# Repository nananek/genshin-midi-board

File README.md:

# RP2040 MIDI → NKRO HID + USB-MIDI

USB MIDI キーボードを USB-A で受け、PC へは NKRO HID キーボード、iPad へは USB-MIDI デバイスとして同時に見せる基板の設計案です。

**RP2040（QFN-56）+ CH345T + 4 層基板**の構成です。外形は **58.0 × 44.0 mm**、四隅 2 mm の 45° パンチカットです。USB-C は長辺に 29.0 mm ピッチで離し、樹脂部が干渉しない余裕を確保します。ケースは無印良品の PP小物ケース M（外寸 64 × 52 × 20 mm、内寸 60 × 46 × 16.5 mm）を使います。加工手順は [docs/case_muji_m.md](docs/case_muji_m.md)、開口用の 1:1 テンプレートは [docs/case_muji_m_template.pdf](docs/case_muji_m_template.pdf) にあります。

> 58.0 × 44.0 mm 基板の配線と検証が完了しました。ERC 0、DRC 0、未接続 0 です。実機検証はまだです。

## 結論

| 項目 | 採用 |
| --- | --- |
| MCU | RP2040 QFN-56 |
| MIDI デバイス側 | CH345T（UART 31250 ↔ USB-MIDI） |
| 基板 | 58.0 × 44.0 × 1.6 mm、4 層、四隅 2 mm パンチカット |
| USB-A | PIO-USB ホスト |
| USB-C 1 | RP2040 native USB、NKRO HID → PC |
| USB-C 2 | CH345T、USB-MIDI → iPad |
| スイッチ | SW1〜SW7（4 × スライド、3 × タクト） |
| 製造 | JLCPCB、4 層、0.5/0.3 mm ビア（最終ホップは 0.45/0.25 mm）、via-in-pad なし |

## 構成の要点

RP2040 の QFN-56 は 0.4 mm ピッチで、外周パッドを外側へ逃がすだけで全ピンを引き出せます。4 層なら GND プレーンを保ちながら標準ビアだけで配線できます。ファームウェアは pico-sdk で、PIO-USB、native USB、UART1 を使います。

詳しい設計は [docs/design.md](docs/design.md) と [docs/decisions.md](docs/decisions.md) を参照してください。データシートとフットプリントの照合は [docs/datasheets.md](docs/datasheets.md) にまとめています。

## 3 ポートの構成

```text
[USB MIDI キーボード]
      │ USB-A (J2)
      ▼
  PIO-USB host (GP12/13)
      │
      ├── Note On/Off ──► RP2040 native USB ── USB-C (J1) ──► PC (NKRO HID)
      │
      └── raw MIDI ── UART1 31250 (GP4/5) ──► CH345T ── USB-C (J3) ──► iPad (USB-MIDI)
```

PC と iPad は物理的に別ポートです。PC 側が未接続でも iPad へ MIDI は流れ、iPad 側が未接続でも PC へ HID は流れます。基板の電源は J1 または J3 の VBUS からダイオード OR で取ります。

## 基板外形とコネクタ

```text
         J1 USB-C (PC)              J3 USB-C (iPad)
         x=15.0                     x=44.0
    ┌────┐                            ┌────┐
    │    │        SW5 RESET           │    │
    │    │           ●                │    │
    ├────┴────────────────────────────┴────┤
    │                                       │
 SW1│                                       │SW3
 SW2│          RP2040 / flash              │
    │          CH345 / power               │
    │                                       │
    ├────┬────────────────────────────┬────┤
    │SW4 │        J2 USB-A            │    │
    └────┘    (MIDI キーボード)        └────┘
```

- 基板: 58.0 × 44.0 mm、t1.6 mm、4 層、四隅 2 mm の 45° パンチカット
- J1/J3: 上長辺、中心間 **29.0 mm**
- J2: 下長辺、USB-A レセプタクル。開口は基板端に合わせる
- J1/J3 の口は基板端から外へ出す。ケースの上壁に 2 か所、下壁に 1 か所の開口を開ける
- Type-C を 10 mm ピッチに寄せるとケーブルの樹脂部が干渉する。今回は同じ失敗を避けるため、29 mm ピッチを確保する

## スイッチ

スイッチは SW1〜SW7 の 7 個です。

| Ref | 部品 | 機能 | 接続 |
| --- | --- | --- | --- |
| SW1 | NKK 115643 スライド | 原神モード（HID ミュート） | GP28 ↔ GND |
| SW2 | NKK 115643 スライド | 楽器モード（スメール音階） | GP15 ↔ GND |
| SW3 | NKK 115643 スライド | サステイン（CC64） | GP27 ↔ GND |
| SW4 | NKK 115643 スライド | USB-A VBUS 手動 ON/OFF | TPS2553 EN 制御 |
| SW5 | DTS-63-N-V-BLK タクト | MIDI リセット（CC123/CC121） | GP14 ↔ GND |
| SW6 | C&K KMR2 SMD タクト | BOOT（QSPI_SS を 1k 経由で GND） | QSPI_SS ↔ GND |
| SW7 | C&K KMR2 SMD タクト | RUN リセット | RUN ↔ GND |

スライドスイッチは 3 ピン品の中央コモンを GPIO、片側を GND、残りを NC にします。GPIO は内部プルアップ、アクティブ LOW、20 ms デバウンスです。SW5 は片側 2 ピンを GND、反対側 2 ピンを GP14 に束ねます。SW6/SW7 は小さな SMD タクトで、ケースの蓋から押します。

## ファイル構成

```text
README.md                         この文書
AGENTS.md                         作業ルール（製造データの配布を含む）
docs/design.md                    詳細設計（電源、ピン、回路、配置）
docs/decisions.md                 設計判断と採用理由
docs/datasheets.md                IC のデータシート、LCSC 型番、CPL 回転の確認
docs/ic_footprints.md             IC フットプリント照合（生成物）
docs/jlcpcb.md                    JLCPCB 向け製造制約と発注チェック
docs/firmware.md                  ファームウェアの実装メモ
docs/case_muji_m.md               無印 PP小物ケース M の加工手順
docs/case_muji_m_template.pdf     開口位置の 1:1 テンプレート
docs/case_muji_m_template.svg     同じテンプレートの SVG
hardware/rp2040_midi_bridge/design.yaml 設計の単一ソース
hardware/rp2040_midi_bridge/pinmap.csv  ピン割り当て
hardware/rp2040_midi_bridge/bom.csv     BOM
hardware/rp2040_midi_bridge/floorplan.svg 配置検討図（生成物）
firmware/include/board_pins.h     ファームウェア用ボード定義
scripts/gen_floorplan.py          配置図生成
scripts/export_ic_footprints.py   IC フットプリント照合の生成
scripts/check_design.py           設計制約チェック
tests/test_design.py              設計制約の単体テスト
```

## 検証

```sh
make check          # 設計制約チェック + 単体テスト
make floorplan      # hardware/rp2040_midi_bridge/floorplan.svg を再生成
make silk           # 基板名、USB-A のピン名、裏面 QR を更新
make case-template  # ケース開口の 1:1 PDF / SVG を再生成
```

`make check` は次を確認します。

- 基板寸法、層数、パンチカット
- USB-C 2 ポートのピッチとエッジ余裕
- ビア径・ドリル径（0.5/0.3 mm と 0.45/0.25 mm、0.15/0.2 mm なし）
- via-in-pad / plugged via の禁止
- ピン割り当ての重複
- スイッチ 7 個の機能と接続
- BOM の SMT 部品に LCSC 型番があること

## 製造データの配布

ガーバー、ドリル、BOM、CPL は設計データとは分けて扱います。リポジトリにはコミットせず、検証済みのリビジョンだけをリリースとして配布します。`make fab VERSION=v0.1.0` で、JLCPCB にそのままアップロードできる Gerber ZIP、BOM、CPL を `dist/` に作ります。Gerber ZIP は展開せず PCB のアップロードへ、BOM と CPL は SMT の欄へ個別に渡します。手順と禁止事項は [AGENTS.md](AGENTS.md) にまとめています。

## ライセンス

[MIT](LICENSE) です。`hardware/rp2040_midi_bridge/lib/` の KiCad シンボルは公式 KiCad ライブラリ由来で、CC-BY-SA 4.0（設計への利用例外あり）です。製造データの配布条件は [AGENTS.md](AGENTS.md) を参照してください。

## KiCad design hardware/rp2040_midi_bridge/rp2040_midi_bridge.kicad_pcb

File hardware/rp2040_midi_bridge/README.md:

# RP2040 MIDI bridge 基板（設計検討）

58.0 × 44.0 mm、4 層、RP2040 + CH345T の設計検討データです。回路図は `rp2040_midi_bridge.kicad_sch` にあり、ERC 0 で通ります。PCB は 58.0 × 44.0 mm の配置で配線済みです。

## 状態

- 外形、配置、回路図、ネットリスト、配線は 58.0 × 44.0 mm で更新済み
- `drc.rpt`（2026-11-25 時点）は 0 DRC violations / 未接続 0
- ガーバー、BOM、CPL は製造前に `make check`、ERC、DRC を通してから生成する

## ファイル

| ファイル | 内容 |
| --- | --- |
| `design.yaml` | 基板、コネクタ、配置、スイッチ、ピン、BOM、製造ルールの正本 |
| `netlist.yaml` | 72 部品、49 ネットのピン接続。回路図と PCB の共通ソース |
| `pinmap.csv` | ピン割り当て（`design.yaml` から生成） |
| `bom.csv` | BOM（`design.yaml` から生成） |
| `placement.csv` | コネクタと主要部品の配置（`design.yaml` から生成） |
| `floorplan.svg` | 配置・干渉検討図（`scripts/gen_floorplan.py` から生成） |
| `rp2040_midi_bridge.kicad_pro` / `.kicad_sch` | KiCad 10 の回路図プロジェクト（`netlist.yaml` から生成） |
| `sym-lib-table` / `fp-lib-table` | プロジェクトローカルと公式のライブラリ参照 |
| `lib/` | 公式に無いシンボルとフットプリント（`lib/README.md` 参照） |
| `erc.rpt` | `kicad-cli sch erc --severity-all` の結果 |
| `rp2040_midi_bridge.kicad_pcb` | KiCad 10 基板（DRC 0 violations、未接続 0） |
| `drc.rpt` | `kicad-cli pcb drc --severity-all` の結果 |

## 再生成

```sh
make tables
make netlist
make floorplan
make check
```

回路図は `netlist.yaml` から生成します。KiCad 10 のコンテナで実行してください。

```sh
./scripts/kicad.sh python3 hardware/rp2040_midi_bridge/scripts/gen_sch.py
make erc
```

## 外形

- 58.0 × 44.0 mm、t1.6 mm
- 四隅 2 mm の 45° パンチカット
- 固定穴なし

## コネクタ

| Ref | 種類 | 位置 | 役割 |
| --- | --- | --- | --- |
| J1 | USB-C | 上辺 x=15.0 | PC / NKRO HID |
| J3 | USB-C | 上辺 x=44.0 | iPad / USB-MIDI |
| J2 | USB-A | 下辺 x=29.0 | MIDI キーボード |

J1/J3 の中心間は 29.0 mm です。Type-C ケーブルの樹脂部が干渉しない余裕を確保しています。ケースは無印 PP小物ケース M（内寸 60 × 46 × 16.5 mm）で、加工手順は [../../docs/case_muji_m.md](../../docs/case_muji_m.md) にあります。

## 注意

このディレクトリのデータは設計検討用です。製造用のガーバーと CPL は含みません。発注前に [../../docs/jlcpcb.md](../../docs/jlcpcb.md) のチェックリストを実行してください。

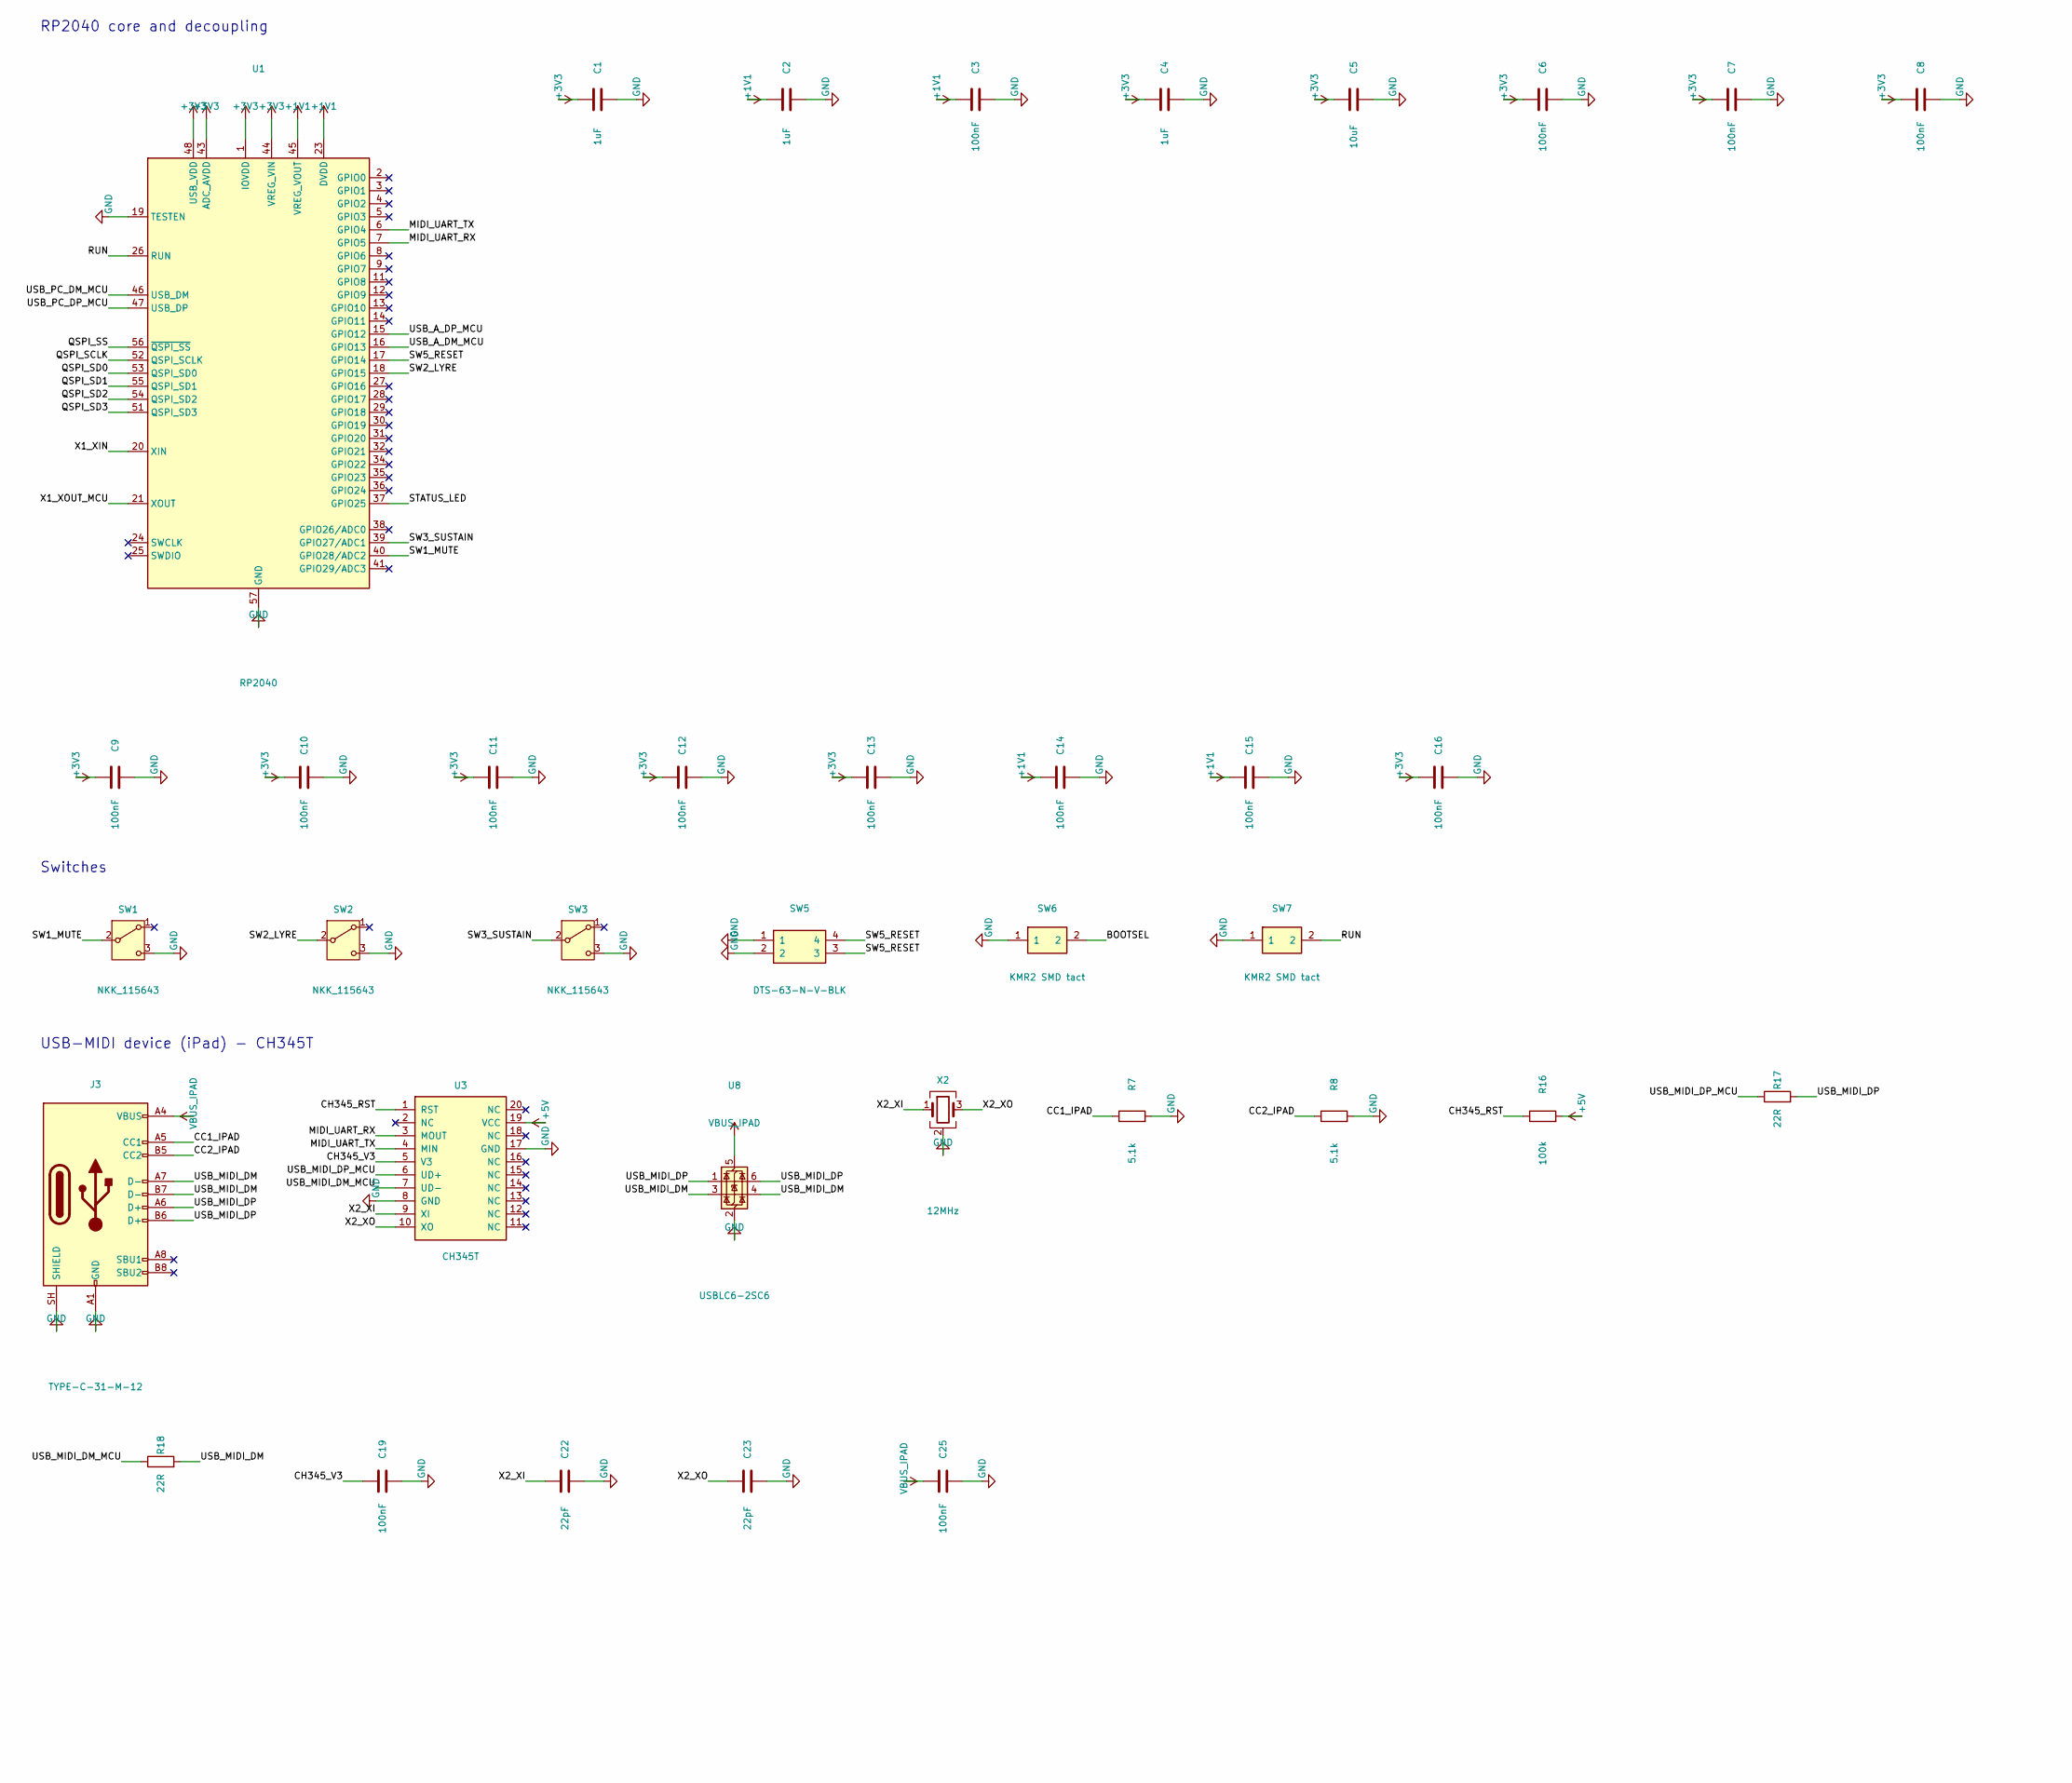
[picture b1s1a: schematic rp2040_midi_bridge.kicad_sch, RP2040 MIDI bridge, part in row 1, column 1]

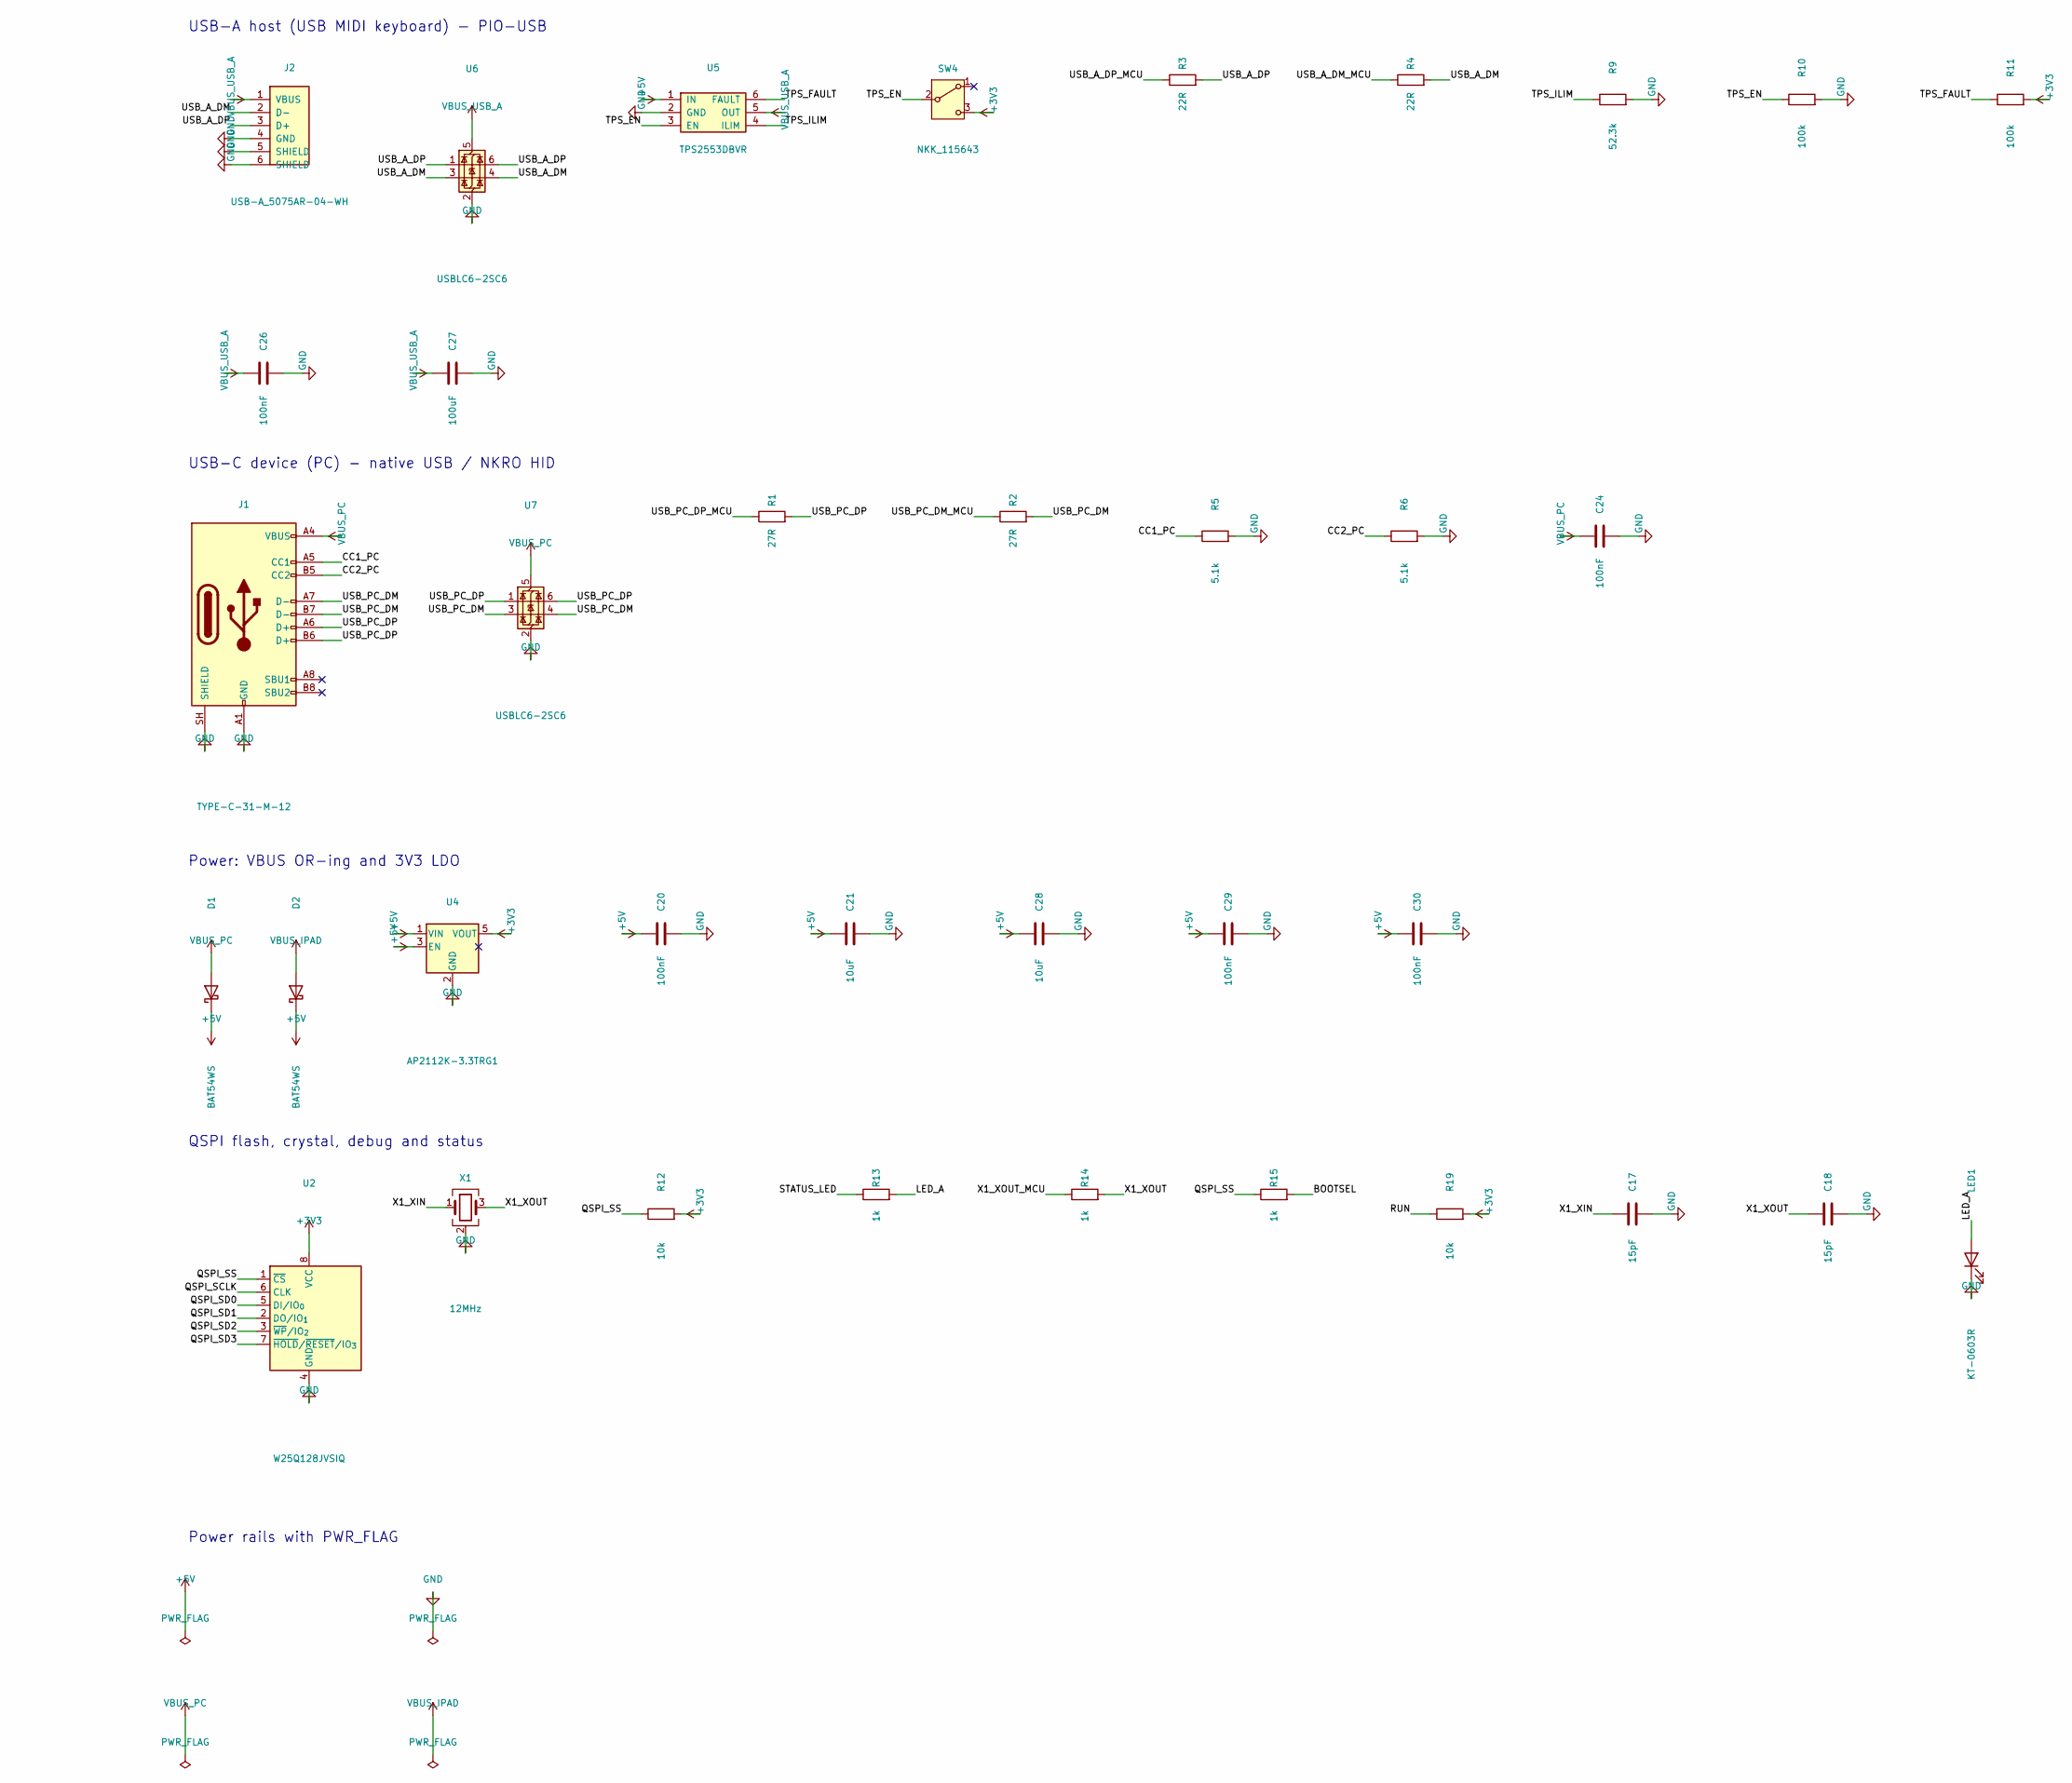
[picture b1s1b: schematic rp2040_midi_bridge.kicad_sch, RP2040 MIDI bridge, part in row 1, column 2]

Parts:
C1, C2, C4: 1uF; C_0603_1608Metric; LCSC C93816
C3, C19, C20, C24, C25, C26, C29, C30: 100nF; C_0603_1608Metric; LCSC C14663
C5, C21, C28: 10uF; C_0805_2012Metric; LCSC C15850
C6, C7, C8, C9, C10, C11, C12, C13, C14, C15, C16: 100nF; C_0603_1608Metric
C17, C18: 15pF; C_0603_1608Metric; LCSC C1548
C22, C23: 22pF; C_0603_1608Metric; LCSC C1653
C27: 100uF; C_1210_3225Metric; LCSC C96123
D1, D2: BAT54WS; D_SOD-323; LCSC C22629
J1, J3: TYPE-C-31-M-12; USB_C_Receptacle_HRO_TYPE-C-31-M-12; LCSC C165948
J2: USB-A_5075AR-04-WH; USB_A_Neltron_5075AR-04-WH
LED1: KT-0603R; LED_0603_1608Metric; LCSC C2286
R1, R2: 27R; R_0603_1608Metric; LCSC C25100
R3, R4, R17, R18: 22R; R_0603_1608Metric; LCSC C23345
R5, R6, R7, R8: 5.1k; R_0603_1608Metric; LCSC C23186
R9: 52.3k; R_0603_1608Metric; LCSC C23198
R10, R11, R16: 100k; R_0603_1608Metric; LCSC C14675
R12, R19: 10k; R_0603_1608Metric; LCSC C25744
R13, R14, R15: 1k; R_0603_1608Metric; LCSC C11702
SW1, SW2, SW3, SW4: NKK_115643; SW_SPDT_NKK_115643_Slide
SW5: DTS-63-N-V-BLK; SW_TACT_Akizuki_DTS63
SW6, SW7: KMR2 SMD tact; SW_Push_1P1T-SH_NO_CK_KMR2xxG; LCSC C2689528
U1: RP2040; QFN-56-1EP_7x7mm_P0.4mm_EP3.2x3.2mm; LCSC C2040
U2: W25Q128JVSIQ; SOIC-8_5.3x5.3mm_P1.27mm; LCSC C97521
U3: CH345T; SSOP-20_5.3x7.2mm_P0.65mm; LCSC C5246448
U4: AP2112K-3.3TRG1; SOT-23-5; LCSC C51118
U5: TPS2553DBVR; SOT-23-6; LCSC C55266
U6, U7, U8: USBLC6-2SC6; SOT-23-6; LCSC C7519
X1, X2: 12MHz; Crystal_SMD_3225-4Pin_3.2x2.5mm; LCSC C50430

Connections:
+1V1: C2.1, C3.1, C14.1, C15.1, U1.23 (DVDD), U1.45 (VREG_VOUT), U1.50 (DVDD)
+3V3: C1.1, C4.1, C5.1, C6.1, C7.1, C8.1, C9.1, C10.1, C11.1, C12.1, C13.1, C16.1, R11.2, R12.2, R19.2, SW4.3 (C), U1.1 (IOVDD), U1.10 (IOVDD), U1.22 (IOVDD), U1.33 (IOVDD), U1.42 (IOVDD), U1.43 (ADC_AVDD), U1.44 (VREG_VIN), U1.48 (USB_VDD), U1.49 (IOVDD), U2.8 (VCC), U4.5 (VOUT)
+5V: C20.1, C21.1, C28.1, C29.1, C30.1, D1.1 (K), D2.1 (K), R16.2, U3.19 (VCC), U4.1 (VIN), U4.3 (EN), U5.1 (IN)
BOOTSEL: R15.2, SW6.2
CC1_IPAD: J3.A5 (CC1), R7.1
CC1_PC: J1.A5 (CC1), R5.1
CC2_IPAD: J3.B5 (CC2), R8.1
CC2_PC: J1.B5 (CC2), R6.1
CH345_RST: R16.1, U3.1 (RST)
CH345_V3: C19.1, U3.5 (V3)
GND: C1.2, C2.2, C3.2, C4.2, C5.2, C6.2, C7.2, C8.2, C9.2, C10.2, C11.2, C12.2, C13.2, C14.2, C15.2, C16.2, C17.2, C18.2, C19.2, C20.2, C21.2, C22.2, C23.2, C24.2, C25.2, C26.2, C27.2, C28.2, C29.2, C30.2, J1.A1 (GND), J1.A12 (GND), J1.B1 (GND), J1.B12 (GND), J1.SH (SHIELD), J2.4 (GND), J2.5 (SHIELD), J2.6 (SHIELD), J3.A1 (GND), J3.A12 (GND), J3.B1 (GND), J3.B12 (GND), J3.SH (SHIELD), LED1.1 (K), R5.2, R6.2, R7.2, R8.2, R9.2, R10.2, SW1.3 (C), SW2.3 (C), SW3.3 (C), SW5.1, SW5.2, SW6.1, SW7.1, U1.19 (TESTEN), U1.57 (GND), U2.4 (GND), U3.8 (GND), U3.17 (GND), U4.2 (GND), U5.2 (GND), U6.2 (GND), U7.2 (GND), U8.2 (GND), X1.2 (G), X1.4 (G), X2.2 (G), X2.4 (G)
LED_A: LED1.2 (A), R13.2
MIDI_UART_RX: U1.7 (GPIO5), U3.3 (MOUT)
MIDI_UART_TX: U1.6 (GPIO4), U3.4 (MIN)
QSPI_SCLK: U1.52 (QSPI_SCLK), U2.6 (CLK)
QSPI_SD0: U1.53 (QSPI_SD0), U2.5 (DI/IO_{0})
QSPI_SD1: U1.55 (QSPI_SD1), U2.2 (DO/IO_{1})
QSPI_SD2: U1.54 (QSPI_SD2), U2.3 (~WP/IO_{2})
QSPI_SD3: U1.51 (QSPI_SD3), U2.7 (~HOLD/~RESET/IO_{3})
QSPI_SS: R12.1, R15.1, U1.56 (~QSPI_SS), U2.1 (~CS)
RUN: R19.1, SW7.2, U1.26 (RUN)
STATUS_LED: R13.1, U1.37 (GPIO25)
SW1_MUTE: SW1.2 (B), U1.40 (GPIO28/ADC2)
SW2_LYRE: SW2.2 (B), U1.18 (GPIO15)
SW3_SUSTAIN: SW3.2 (B), U1.39 (GPIO27/ADC1)
SW5_RESET: SW5.3, SW5.4, U1.17 (GPIO14)
TPS_EN: R10.1, SW4.2 (B), U5.3 (EN)
TPS_FAULT: R11.1, U5.6 (FAULT)
TPS_ILIM: R9.1, U5.4 (ILIM)
USB_A_DM: J2.2 (D-), R4.2, U6.3 (I/O2), U6.4 (I/O2)
USB_A_DM_MCU: R4.1, U1.16 (GPIO13)
USB_A_DP: J2.3 (D+), R3.2, U6.1 (I/O1), U6.6 (I/O1)
USB_A_DP_MCU: R3.1, U1.15 (GPIO12)
USB_MIDI_DM: J3.A7 (D-), J3.B7 (D-), R18.2, U8.3 (I/O2), U8.4 (I/O2)
USB_MIDI_DM_MCU: R18.1, U3.7 (UD-)
USB_MIDI_DP: J3.A6 (D+), J3.B6 (D+), R17.2, U8.1 (I/O1), U8.6 (I/O1)
USB_MIDI_DP_MCU: R17.1, U3.6 (UD+)
USB_PC_DM: J1.A7 (D-), J1.B7 (D-), R2.2, U7.3 (I/O2), U7.4 (I/O2)
USB_PC_DM_MCU: R2.1, U1.46 (USB_DM)
USB_PC_DP: J1.A6 (D+), J1.B6 (D+), R1.2, U7.1 (I/O1), U7.6 (I/O1)
USB_PC_DP_MCU: R1.1, U1.47 (USB_DP)
VBUS_IPAD: C25.1, D2.2 (A), J3.A4 (VBUS), J3.A9 (VBUS), J3.B4 (VBUS), J3.B9 (VBUS), U8.5 (VBUS)
VBUS_PC: C24.1, D1.2 (A), J1.A4 (VBUS), J1.A9 (VBUS), J1.B4 (VBUS), J1.B9 (VBUS), U7.5 (VBUS)
VBUS_USB_A: C26.1, C27.1, J2.1 (VBUS), U5.5 (OUT), U6.5 (VBUS)
X1_XIN: C17.1, U1.20 (XIN), X1.1
X1_XOUT: C18.1, R14.2, X1.3
X1_XOUT_MCU: R14.1, U1.21 (XOUT)
X2_XI: C22.1, U3.9 (XI), X2.1
X2_XO: C23.1, U3.10 (XO), X2.3

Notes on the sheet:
RP2040 core and decoupling
Switches
USB-MIDI device (iPad) - CH345T
USB-A host (USB MIDI keyboard) - PIO-USB
USB-C device (PC) - native USB / NKRO HID
Power: VBUS OR-ing and 3V3 LDO
QSPI flash, crystal, debug and status
Power rails with PWR_FLAG

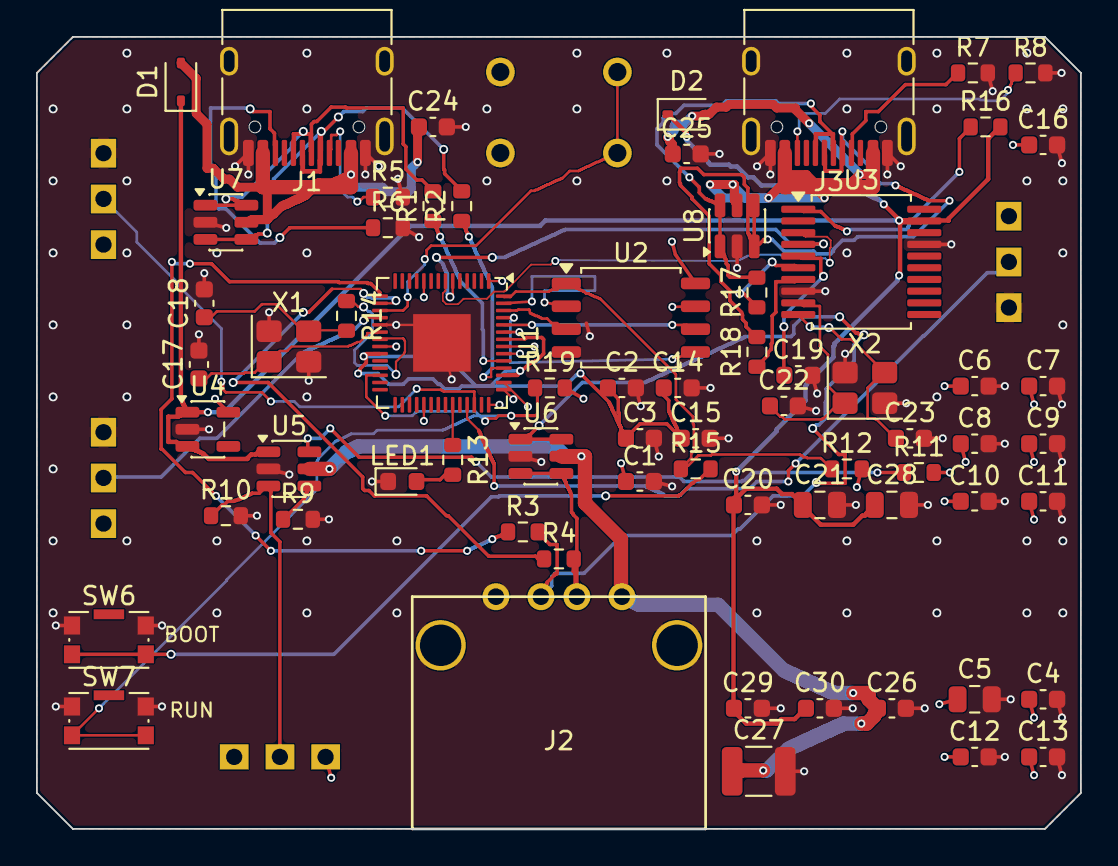
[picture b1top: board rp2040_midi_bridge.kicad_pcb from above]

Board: 4 copper layers, 58.0 x 44.0 mm, 72 parts (0 on the bottom side), 49 nets.

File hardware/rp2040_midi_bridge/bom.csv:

ref,value,footprint,lcsc,assembly,note
U1,RP2040,QFN-56 7x7 mm,C2040,SMT,-
U2,W25Q128JVSIQ,SOIC-8 5.3x5.3 mm,C97521,SMT,-
U3,CH345T,SSOP-20 5.3x7.2 mm P0.65,C5246448,SMT,-
U4,AP2112K-3.3TRG1,SOT-23-5,C51118,SMT,LCSC 型番は発注前に再確認
U5,TPS2553DBVR,SOT-23-6,C55266,SMT,-
"U6,U7,U8",USBLC6-2SC6,SOT-23-6,C7519,SMT,-
"D1,D2",BAT54WS,SOD-323,C22629,SMT,-
"X1,X2",12MHz,3225-4pin,C50430,SMT,-
"J1,J3",TYPE-C-31-M-12,USB-C 16P,C165948,SMT,シェル固定タブは THT。JLCPCB の実装プレビューで向きを確認
J2,USB-A 5075AR-04-WH,USB-A THT,,THT,Akizuki 100160。手はんだ
SW1-SW4,NKK 115643,SPDT slide 3pin,,THT,Akizuki 115643。手はんだ。4 個（SW1/SW2/SW3/SW4）
SW5,DTS-63-N-V-BLK,tact 4pin,,THT,Akizuki 103647。手はんだ。MIDI reset
"R1,R2",27R,0603,C25100,SMT,-
"R3,R4,R17,R18",22R,0603,C23345,SMT,USB-A 側 2 本、CH345T 側 2 本
"R5,R6,R7,R8",5.1k,0603,C23186,SMT,-
R9,52.3k 1%,0603,C23198,SMT,-
"R10,R11,R16",100k 1%,0603,C14675,SMT,-
"R12,R19",10k,0603,C25744,SMT,-
"R13,R14,R15",1k,0603,C11702,SMT,-
"C3,C6-C16,C19,C20,C24,C25,C26,C29,C30",100nF,0603,C14663,SMT,-
"C1,C2,C4",1uF,0603,C93816,SMT,-
"C5,C21,C28",10uF,0805,C15850,SMT,-
"C17,C18",15pF,0603,C1548,SMT,-
"C22,C23",22pF,0603,C1653,SMT,-
C27,100uF 10V,C_1210_3225Metric,C96123,SMT,USB-A VBUS バルク。1210 セラミック。LCSC 型番は発注前に再確認
LED1,red 0603,0603,C2286,SMT,-
"SW6,SW7",KMR2 SMD tact,SMD 4.2x2.2,C2689528,SMT,BOOT / RUN。SMT 実装可、手はんだでも可

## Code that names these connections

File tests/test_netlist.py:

from __future__ import annotations

import unittest
from pathlib import Path

import yaml

ROOT = Path(__file__).resolve().parent.parent
NETLIST = yaml.safe_load((ROOT / "hardware" / "rp2040_midi_bridge" / "netlist.yaml").read_text(encoding="utf-8"))


class NetlistTests(unittest.TestCase):
    def test_component_and_net_counts(self) -> None:
        self.assertEqual(len(NETLIST["components"]), 72)
        self.assertEqual(len(NETLIST["nets"]), 49)

    def test_every_net_has_at_least_two_pins(self) -> None:
        for net, members in NETLIST["nets"].items():
            self.assertGreaterEqual(len(members), 2, net)

    def test_every_component_has_a_footprint(self) -> None:
        for ref, comp in NETLIST["components"].items():
            self.assertTrue(comp["footprint"], ref)

    def test_pins_are_not_reused_within_a_component(self) -> None:
        for ref, comp in NETLIST["components"].items():
            pins = list(comp["pins"])
            self.assertEqual(len(pins), len(set(pins)), ref)

    def test_usb_pairs_are_present(self) -> None:
        nets = NETLIST["nets"]
        for net in ("USB_A_DP", "USB_A_DM", "USB_PC_DP", "USB_PC_DM", "USB_MIDI_DP", "USB_MIDI_DM"):
            self.assertIn(net, nets)
            self.assertGreaterEqual(len(nets[net]), 2, net)

    def test_power_nets_have_sources_and_loads(self) -> None:
        nets = NETLIST["nets"]
        for net in ("+5V", "+3V3", "+1V1", "GND", "VBUS_PC", "VBUS_IPAD", "VBUS_USB_A"):
            self.assertIn(net, nets)
            self.assertGreaterEqual(len(nets[net]), 2, net)

    def test_switches_match_the_design(self) -> None:
        comps = NETLIST["components"]
        self.assertEqual(comps["SW1"]["pins"]["2"], "SW1_MUTE")
        self.assertEqual(comps["SW2"]["pins"]["2"], "SW2_LYRE")
        self.assertEqual(comps["SW3"]["pins"]["2"], "SW3_SUSTAIN")
        self.assertEqual(comps["SW4"]["pins"]["2"], "TPS_EN")
        self.assertEqual(comps["SW5"]["pins"]["3"], "SW5_RESET")
        self.assertEqual(comps["SW6"]["pins"]["2"], "BOOTSEL")
        self.assertEqual(comps["SW7"]["pins"]["2"], "RUN")

    def test_rp2040_usb_and_qspi_pins(self) -> None:
        pins = NETLIST["components"]["U1"]["pins"]
        self.assertEqual(pins["46"], "USB_PC_DM_MCU")
        self.assertEqual(pins["47"], "USB_PC_DP_MCU")
        self.assertEqual(pins["15"], "USB_A_DP_MCU")
        self.assertEqual(pins["16"], "USB_A_DM_MCU")
        self.assertEqual(pins["51"], "QSPI_SD3")
        self.assertEqual(pins["56"], "QSPI_SS")
        self.assertEqual(pins["57"], "GND")


if __name__ == "__main__":
    unittest.main()

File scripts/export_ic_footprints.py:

#!/usr/bin/env python3
"""Export the IC footprints from the routed board for datasheet comparison.

Run inside the KiCad container:

    make ic-footprints

Writes docs/ic_footprints.md.  The datasheet package data below is the
reference; the board is the source of the footprint names, pad counts,
pad row spacing, pitch and pad-1 net.
"""

from __future__ import annotations

from collections import Counter
from pathlib import Path

import pcbnew

ROOT = Path(__file__).resolve().parent.parent
PCB = ROOT / "hardware" / "rp2040_midi_bridge" / "rp2040_midi_bridge.kicad_pcb"
OUT = ROOT / "docs" / "ic_footprints.md"

TOMM = pcbnew.ToMM

# Datasheet package references and the expected pad-1 net.
DATASHEET = {
    "U1": {
        "part": "RP2040",
        "package": "QFN-56 7x7 mm, 0.4 mm, EP 3.2x3.2 mm (61 pads: 56 + EP/thermal)",
        "pads": 61,
        "row": 6.875,
        "pitch": 0.4,
        "pin1": "+3V3",
    },
    "U2": {
        "part": "W25Q128JVSIQ",
        "package": "SOIC-8 208-mil (5.28x5.18 mm body, 7.17 mm pad row), 1.27 mm",
        "pads": 8,
        "row": 7.17,
        "pitch": 1.27,
        "pin1": "QSPI_SS",
    },
    "U3": {
        "part": "CH345T",
        "package": "SSOP-20 5.3x7.2 mm body, 7.0 mm pad row, 0.65 mm",
        "pads": 20,
        "row": 7.0,
        "pitch": 0.65,
        "pin1": "CH345_RST",
    },
    "U4": {
        "part": "AP2112K-3.3TRG1",
        "package": "SOT-23-5",
        "pads": 5,
        "row": 2.27,
        "pitch": 0.95,
        "pin1": "+5V",
    },
    "U5": {
        "part": "TPS2553DBVR",
        "package": "SOT-23-6",
        "pads": 6,
        "row": 2.27,
        "pitch": 0.95,
        "pin1": "+5V",
    },
    "U6": {
        "part": "USBLC6-2SC6",
        "package": "SOT-23-6",
        "pads": 6,
        "row": 2.27,
        "pitch": 0.95,
        "pin1": "USB_A_DP",
    },
    "U7": {
        "part": "USBLC6-2SC6",
        "package": "SOT-23-6",
        "pads": 6,
        "row": 2.27,
        "pitch": 0.95,
        "pin1": "USB_PC_DP",
    },
    "U8": {
        "part": "USBLC6-2SC6",
        "package": "SOT-23-6",
        "pads": 6,
        "row": 2.27,
        "pitch": 0.95,
        "pin1": "USB_MIDI_DP",
    },
}


def unique(values: list[float]) -> list[float]:
    out: list[float] = []
    for value in sorted(values):
        if not out or abs(value - out[-1]) > 0.001:
            out.append(value)
    return out


def pitch_of(*groups: list[float]) -> float:
    steps = [
        round(b - a, 4)
        for values in groups
        for a, b in zip(values, values[1:])
        if b - a > 0.001
    ]
    if not steps:
        return 0.0
    return Counter(steps).most_common(1)[0][0]


def footprint_name(fp: pcbnew.FOOTPRINT) -> str:
    fpid = fp.GetFPID()
    lib = fpid.GetLibNickname()
    item = fpid.GetLibItemName()
    return f"{lib}:{item}" if lib else item


def main() -> None:
    board = pcbnew.LoadBoard(str(PCB))
    rows: list[str] = []
    notes: list[str] = []

    for ref, expected in DATASHEET.items():
        fp = board.FindFootprintByReference(ref)
        if fp is None:
            rows.append(f"| {ref} | {expected['part']} | missing | - | - | - | - | - | MISSING |")
            notes.append(f"{ref}: footprint not found")
            continue

        pads = list(fp.Pads())
        xs = [TOMM(p.GetPosition().x) for p in pads]
        ys = [TOMM(p.GetPosition().y) for p in pads]
        ux = unique(xs)
        uy = unique(ys)
        row = max(max(xs) - min(xs), max(ys) - min(ys))
        pitch = pitch_of(ux, uy)

        pad1 = fp.FindPadByNumber("1")
        pad1_net = pad1.GetNetname() if pad1 else ""
        pad1_ok = pad1_net == expected["pin1"]
        row_ok = abs(row - expected["row"]) <= 0.1
        pitch_ok = abs(pitch - expected["pitch"]) <= 0.01
        pads_ok = len(pads) == expected["pads"]
        ok = pad1_ok and row_ok and pitch_ok and pads_ok

        verdict = "OK" if ok else "MISMATCH"
        rows.append(
            f"| {ref} | {expected['part']} | `{footprint_name(fp)}` | {len(pads)} | "
            f"{row:.2f} | {pitch:.2f} | {expected['package']} | "
            f"`{pad1_net}` | {verdict} |"
        )
        if not ok:
            reasons = []
            if not pads_ok:
                reasons.append(f"pad count {len(pads)} != {expected['pads']}")
            if not row_ok:
                reasons.append(f"pad row {row:.2f} != {expected['row']:.2f}")
            if not pitch_ok:
                reasons.append(f"pitch {pitch:.2f} != {expected['pitch']:.2f}")
            if not pad1_ok:
                reasons.append(f"pad1 net {pad1_net} != {expected['pin1']}")
            notes.append(f"{ref}: " + ", ".join(reasons))

    lines = [
        "# IC フットプリント照合",
        "",
        "Generated by `scripts/export_ic_footprints.py` from the routed board. "
        "Do not edit; run `make ic-footprints` to update.",
        "",
        "| Ref | 型番 | KiCad footprint | Pads | パッド列間 (mm) | ピッチ (mm) | データシート package | pad1 ネット | 判定 |",
        "| --- | --- | --- | ---: | ---: | ---: | --- | --- | --- |",
        *rows,
        "",
    ]
    if notes:
        lines.append("## 不一致")
        lines.append("")
        for note in notes:
            lines.append(f"- {note}")
        lines.append("")
    if any(note.startswith("U2:") for note in notes):
        lines.append(
            "U2 のフットプリントが W25Q128JVSIQ の 208-mil パッケージと一致していない。"
            "`SOIC-8_5.3x5.3mm_P1.27mm` を使う。"
        )
    elif notes:
        lines.append("上記の IC はデータシートのパッケージと一致していない。")
    else:
        lines.append("すべての IC のフットプリントがデータシートのパッケージと一致している。")
    lines.append("")
    OUT.write_text("\n".join(lines), encoding="utf-8")
    print(f"wrote {OUT}")


if __name__ == "__main__":
    main()

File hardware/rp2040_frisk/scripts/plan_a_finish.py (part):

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]
PRE_STRIP = QSPI + ["TPS_FAULT"]

QSPI_PINS = {"QSPI_SS": ("56", "1"), "QSPI_SCLK": ("52", "6"),
             "QSPI_SD0": ("53", "5"), "QSPI_SD1": ("55", "2"),
             "QSPI_SD2": ("54", "3"), "QSPI_SD3": ("51", "7")}

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    remove_board_net(board, copper, "MIDI_UART_TX")
    remove_board_net(board, copper, "MIDI_UART_RX")
    _, u3pads = pad_map(board, "U3")
    for net, upin, pq in (("MIDI_UART_TX", "6", "4"),
                          ("MIDI_UART_RX", "7", "3")):
        src = (*T(u1pads[upin].GetPosition()), "F")
        dst = (*T(u3pads[pq].GetPosition()), "F")
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    b.add_via("SW3_SUSTAIN", (25.0, 22.4), 0.25, 0.225)
    _, sw3pads = pad_map(board, "SW3")
    pin2 = T(sw3pads["2"].GetPosition())
    good = b.connect("SW3_SUSTAIN", (25.0, 22.4, "B"), (*pin2, "FB"),
                     [0.15, 0.127], forces=(1,), vcs=(30, 8))
    print(f"SW3_SUSTAIN: {'ok' if good else 'FAIL'}", flush=True)
    ok &= good
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
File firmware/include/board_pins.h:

#ifndef BOARD_PINS_H
#define BOARD_PINS_H

// RP2040 MIDI bridge (design study)
//
// The pin names are kept independent of the board so that config.h can use
// them directly.  RP2040 QSPI uses pins 51-56, not GPIO0-5, so GP0/1 remain
// available for the debug UART.

#define PIN_USB_HOST_DP 12
#define PIN_USB_HOST_DM 13

#define MIDI_UART_INDEX 1
#define MIDI_UART_TX_PIN 4
#define MIDI_UART_RX_PIN 5

#define MUTE_SWITCH_PIN 28
#define LYRE_SWITCH_PIN 15
#define SUSTAIN_SWITCH_PIN 27
#define MIDI_RESET_BUTTON_PIN 14

#define STATUS_LED_PIN 25

#define DEBUG_UART_TX_PIN 0
#define DEBUG_UART_RX_PIN 1

#define BOARD_TUH_RHPORT 1
#define BOARD_TUD_RHPORT 0

#define MIDI_RESET_DEBOUNCE_MS 20
#define SUSTAIN_DEBOUNCE_MS 20

#endif // BOARD_PINS_H
